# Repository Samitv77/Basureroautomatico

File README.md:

# Basureroautomatico

# Resumen 
El proyecto propuesto para el desarrollo de un contenedor de residuos automático con tecnología ESP32 tiene un enfoque integral, abordando desafíos actuales en la gestión de residuos en lugares públicos. El alcance del proyecto se ha delineado cuidadosamente, incluyendo objetivos específicos, inclusiones, exclusiones, restricciones y un cronograma detallado.

El objetivo general de optimizar la recolección de residuos en áreas públicas, aumentando la eficiencia operativa y reduciendo la contaminación ambiental, se desglosa en objetivos específicos que abarcan desde el diseño del prototipo hasta la evaluación del rendimiento del sistema en entornos de prueba simulados.

La inclusión de tecnología ESP32, sensores ultrasónicos y un actuador (servomotor) es esencial para la detección precisa del nivel de llenado y la apertura controlada del contenedor. La programación a través de Thonny IDE con MicroPython asegura la interacción efectiva entre estos componentes.

El desarrollo de un algoritmo de control inteligente es clave para la automatización del proceso, permitiendo la apertura automática del contenedor cuando se detecta un nivel de llenado crítico. Esta característica contribuye a la optimización de la eficiencia de la recolección de residuos.

El alcance del proyecto incluye la validación del prototipo en entornos de prueba simulados para evaluar la efectividad y confiabilidad del sistema. Sin embargo, se excluye la producción a gran escala y la integración total en la infraestructura urbana existente, centrándose en la validación del concepto a nivel de prototipo.

Se establecen restricciones en términos de recursos técnicos y un límite presupuestario para garantizar una implementación económica y sostenible del proyecto.

El cronograma proporcionado guía el progreso del proyecto desde la fase de diseño hasta la evaluación y retroalimentación. Las fases de adquisición de materiales, desarrollo del código, integración de componentes, implementación del algoritmo y pruebas, validación en entornos de prueba, y documentación y presentación, están claramente definidas.

La última semana se reserva para la evaluación del prototipo y la recopilación de retroalimentación, permitiendo ajustes finales y mejoras basadas en los resultados obtenidos durante todo el desarrollo del proyecto.

El proyecto aborda de manera integral la gestión de residuos en entornos públicos, proponiendo una solución tecnológica innovadora que podría tener un impacto positivo en la eficiencia operativa y la reducción de la contaminación ambiental.

# Problematica
En entornos urbanos y lugares con mucha gente, la gestión de residuos es un desafío. La acumulación desigual de basura afecta la estética, la salud pública y el medio ambiente. La recogida manual tradicional es ineficiente y crea problemas. Esto lo podemos observar acá y en cualquier país Latinoamericano, por ende, es necesario hacer soluciones de forma que reduzcan este problema. Se Propone un contenedor automático con tecnología ESP32 que detecta y abre automáticamente según el nivel de llenado. Esto mejora la eficiencia al asignar recursos según la demanda real. La tecnología no solo optimiza la recolección de basura, sino que también reduce la contaminación ambiental al minimizar la exposición de residuos al aire libre.
Esta solución innovadora aborda los desafíos actuales de la gestión de residuos en lugares públicos, buscando una respuesta sostenible y tecnológica para mejorar la calidad ambiental en entornos urbanos con alta afluencia de personas.

# Alcance
En fase, el proyecto delinea claramente su alcance, enfocándose en la implementación de un basurero automatizado. El objetivo principal es proporcionar a los usuarios una experiencia única, caracterizada por la facilidad de uso y accesibilidad universal. La incorporación de elementos visuales, como LEDs, se contempla para mejorar la interacción del usuario con el basurero y garantizar una gestión eficiente de los residuos.

# Objetivos

Objetivo Especifico
•	Desarrollar e implementar un sistema automatizado de gestión de residuos mediante un contenedor de basura con tecnología ESP32 que optimice la recolección de residuos en áreas públicas, aumentando la eficiencia operativa y ayudando a reducir la contaminación ambiental.

Objetivos Generales

•	Diseñar y crear un prototipo de un bote de basura automático que pueda detectar con precisión su nivel de llenado mediante sensores integrados.
•	Programe el sistema utilizando Thonny IDE con MicroPython, asegurándose de que el ESP32, los sensores y el actuador (servomotor) interactúen correctamente.
•	Implemente un algoritmo de control que le permita abrir automáticamente el bote de basura cuando se detecte un nivel de llenado crítico, facilitando la recolección de residuos.

# Impactos 

# Diseño: Caja Negra

[CAja_negra_diagrama (2).pdf](https://github.com/Samitv77/Basureroautomatico/files/13495587/CAja_negra_diagrama.2.pdf)

# Diseño Diagrama Tecnologico 

[Diagrama Tecnologico.pdf](https://github.com/Samitv77/Basureroautomatico/files/13495593/Diagrama.Tecnologico.pdf)

# Esquematico 
Cuaderno

Kicad

# Esquematico PCB y PCB creada
Kicad

Impresa

Visor 3D

# Conclusiones

Este proyecto tiene varios puntos a favor:
1.	La introducción de un sistema automatizado de gestión de residuos: aborda directamente la problemática de la acumulación descontrolada. Al incorporar el sensor ultrasónico y el servomotor, se logra una recolección más precisa y oportuna, evitando desbordamientos y ayudando a la preservación del entorno.

2.	La elección del ESP32 como plataforma central: destaca la importancia de la versatilidad y programabilidad en la implementación de soluciones tecnológicas. Esta elección no solo facilita la interacción sin problemas entre los componentes del sistema, sino que también permite adaptarse a futuras mejoras y actualizaciones.

3.	Su funcionalidad técnica: este cubo de basura automático se integra perfectamente en la visión de entornos urbanos más limpios y sostenibles. La combinación de tecnología y conciencia ambiental refuerza la idea de que la innovación puede desempeñar un papel clave en la transformación positiva de nuestras comunidades.

El proyecto no solo  propone una solución eficiente para el manejo de residuos en espacios públicos, sino que también se presenta como una idea útil de cómo la tecnología, cuando se aplica de manera inteligente, puede contribuir significativamente a la construcción de un futuro más sostenible y saludable.

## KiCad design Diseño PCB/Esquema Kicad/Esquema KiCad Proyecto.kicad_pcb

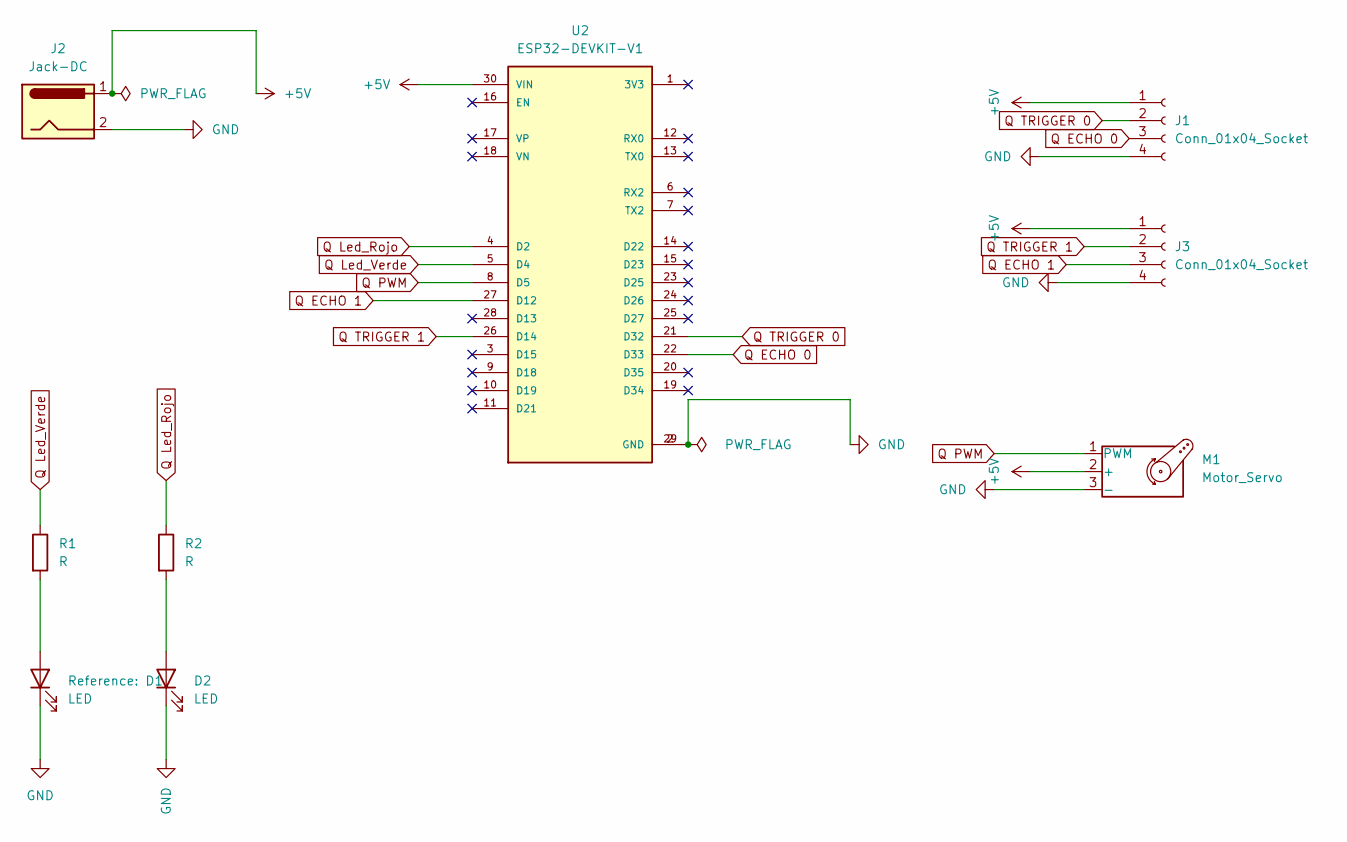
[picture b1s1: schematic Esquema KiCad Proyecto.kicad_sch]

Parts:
D1, D2: LED; LED_D1.8mm_W1.8mm_H2.4mm_Horizontal_O1.27mm_Z1.6mm
J1, J3: Conn_01x04_Socket; PinSocket_1x04_P2.54mm_Vertical
J2: Jack-DC; BarrelJack_CUI_PJ-102AH_Horizontal
M1: Motor_Servo; PinHeader_1x03_P2.54mm_Vertical
R1, R2: R; R_Axial_DIN0411_L9.9mm_D3.6mm_P12.70mm_Horizontal
U2: ESP32-DEVKIT-V1; MODULE_ESP32_DEVKIT_V1; PARTREV N/A

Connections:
+5V: J1.1, J2.1, J3.1, M1.2 (+), U2.30 (VIN)
GND: D1.1 (K), D2.1 (K), J1.4, J2.2, J3.4, M1.3 (-), U2.2 (GND), U2.29 (GND)
unnamed: D1.2 (A), R1.2
unnamed: D2.2 (A), R2.2
Q ECHO 0: J1.3, U2.22 (D33)
Q ECHO 1: J3.3, U2.27 (D12)
Q Led_Rojo: R2.1, U2.4 (D2)
Q Led_Verde: R1.1, U2.5 (D4)
Q PWM: M1.1 (PWM), U2.8 (D5)
Q TRIGGER 0: J1.2, U2.21 (D32)
Q TRIGGER 1: J3.2, U2.26 (D14)

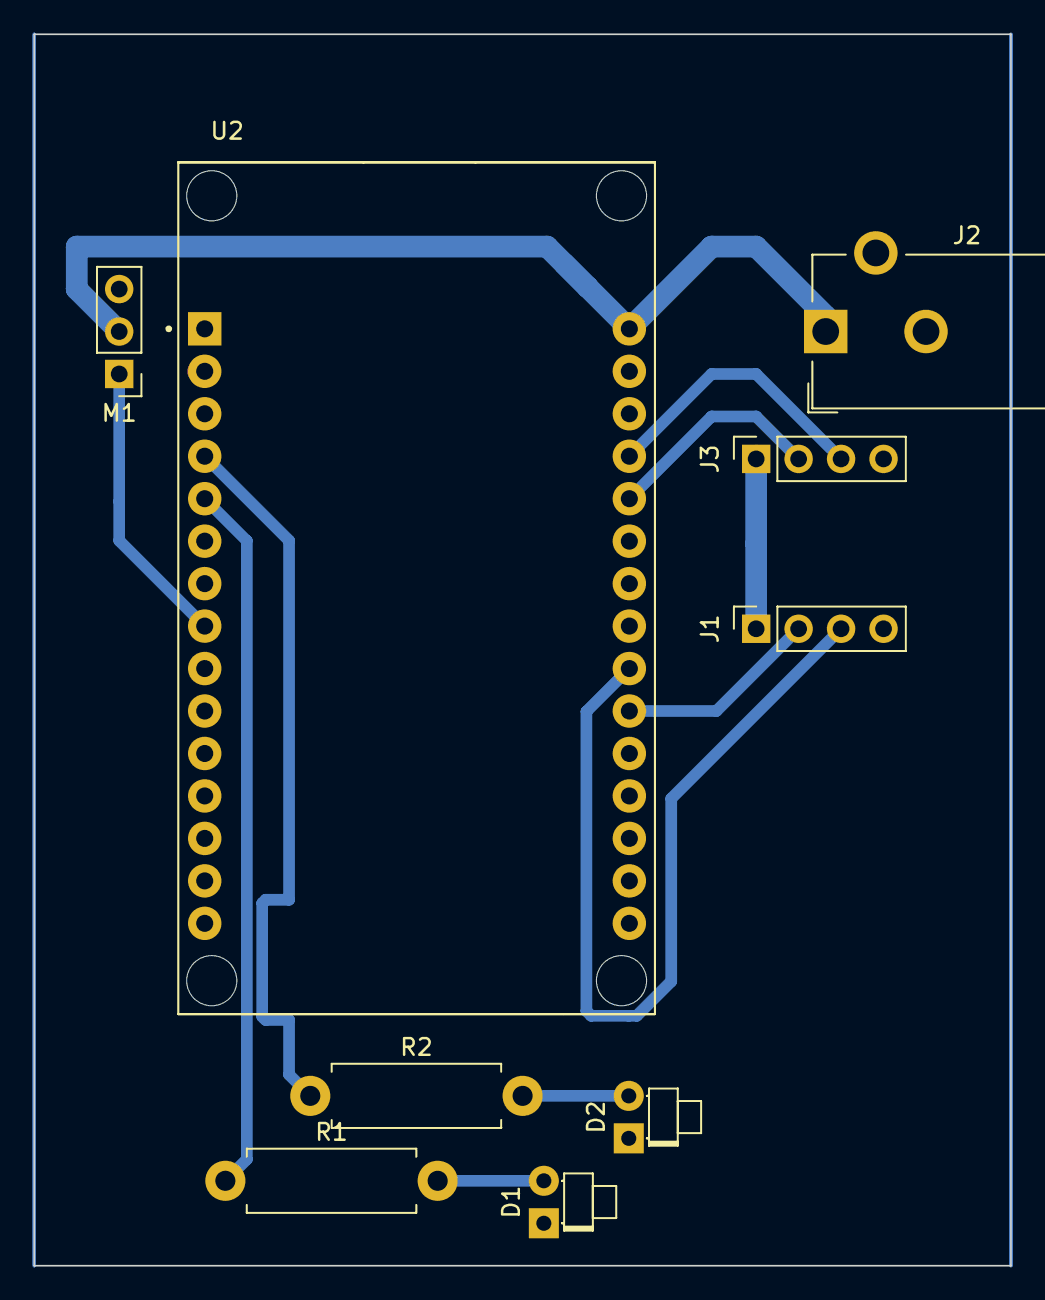
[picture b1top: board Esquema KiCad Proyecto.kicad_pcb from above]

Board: 2 copper layers, 58.4 x 73.7 mm, 9 parts (0 on the bottom side), 11 nets.

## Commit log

2023-11-26 Add files via upload
    Caja Negra - Basurero Automático
2023-11-26 README.md
2023-12-01 Create Pruebasensorleds
2023-12-01 Rename Pruebasensorleds to Software/pruebaSensorLeds
2023-12-01 Create PruebaSensorServo
2023-12-01 Create CodigoCompleto
2023-12-01 Create Diseño PCB
2023-12-01 Create Gerbers
2023-12-01 Create PCB Gerbers
2023-12-01 Create Archivos
2023-12-01 Create Imagenes
